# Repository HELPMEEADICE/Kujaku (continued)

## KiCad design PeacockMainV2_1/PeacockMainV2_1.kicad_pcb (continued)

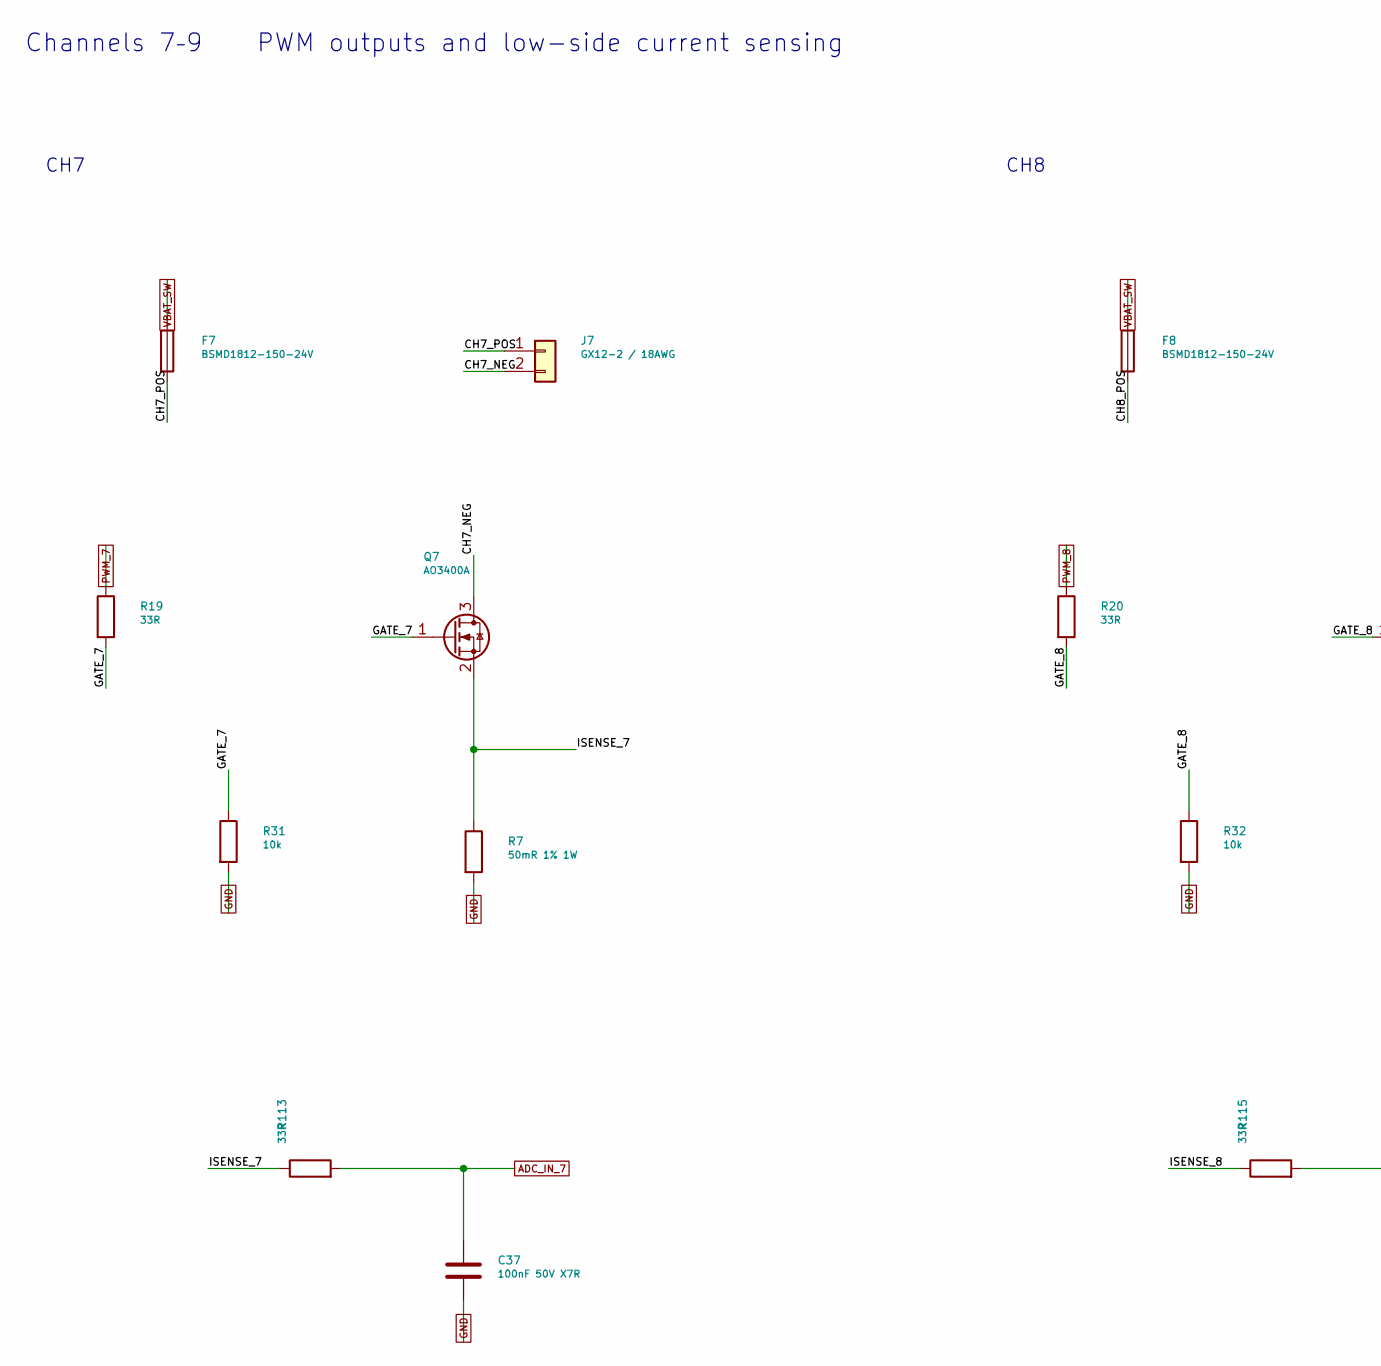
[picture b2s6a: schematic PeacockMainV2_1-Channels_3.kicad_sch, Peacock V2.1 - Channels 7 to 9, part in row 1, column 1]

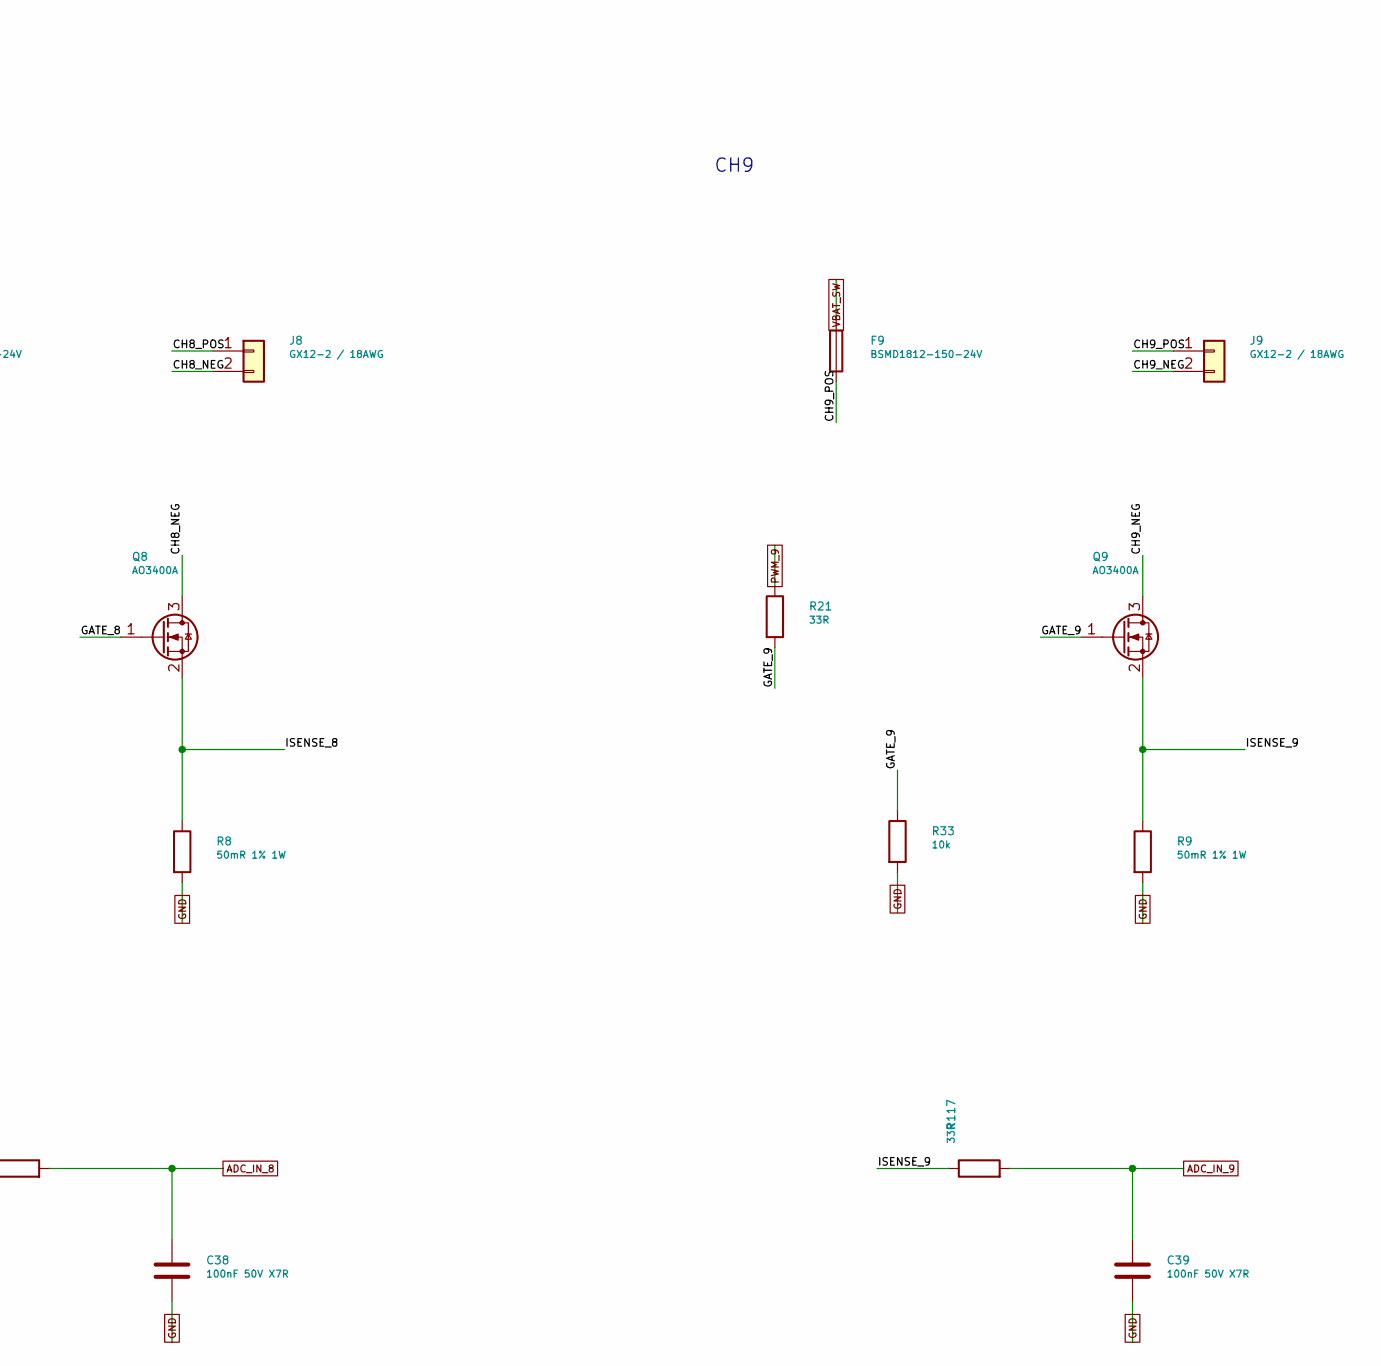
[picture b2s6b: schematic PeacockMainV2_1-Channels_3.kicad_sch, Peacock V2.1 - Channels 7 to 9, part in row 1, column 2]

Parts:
C37, C38, C39: 100nF 50V X7R; C_0603_1608Metric; MPN CC0603KRX7R9BB104; LCSC C14663
F7, F8, F9: BSMD1812-150-24V; R_1812_4532Metric; MPN BSMD1812-150-24V; LCSC C883153
J7, J8, J9: GX12-2 / 18AWG; GX12_Leadout_1x02_P5.00mm
Q7, Q8, Q9: AO3400A; SOT-23; MPN AO3400A; LCSC C20917
R7, R8, R9: 50mR 1% 1W; R_1206_3216Metric; MPN FRM121WFR050TM; LCSC C7467249
R19, R20, R21, R113, R115, R117: 33R; R_0603_1608Metric; MPN 0603WAF330JT5E; LCSC C23140
R31, R32, R33: 10k; R_0603_1608Metric; MPN 0603WAF1002T5E; LCSC C25804

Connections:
/Channels 3/CH7_NEG: J7.2, Q7.3 (D)
/Channels 3/CH7_POS: F7.2, J7.1
/Channels 3/CH8_NEG: J8.2, Q8.3 (D)
/Channels 3/CH8_POS: F8.2, J8.1
/Channels 3/CH9_NEG: J9.2, Q9.3 (D)
/Channels 3/CH9_POS: F9.2, J9.1
/Channels 3/GATE_7: Q7.1 (G), R19.2, R31.1
/Channels 3/GATE_8: Q8.1 (G), R20.2, R32.1
/Channels 3/GATE_9: Q9.1 (G), R21.2, R33.1
/Channels 3/ISENSE_7: Q7.2 (S), R7.1, R113.1
/Channels 3/ISENSE_8: Q8.2 (S), R8.1, R115.1
/Channels 3/ISENSE_9: Q9.2 (S), R9.1, R117.1
ADC_IN_7: C37.1, R113.2; also elsewhere on the board
ADC_IN_8: C38.1, R115.2; also elsewhere on the board
ADC_IN_9: C39.1, R117.2; also elsewhere on the board
GND: C37.2, C38.2, C39.2, R7.2, R8.2, R9.2, R31.2, R32.2, R33.2; also elsewhere on the board
PWM_7: R19.1; also elsewhere on the board
PWM_8: R20.1; also elsewhere on the board
PWM_9: R21.1; also elsewhere on the board
VBAT_SW: F7.1, F8.1, F9.1; also elsewhere on the board

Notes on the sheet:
Channels 7–9 PWM outputs and low-side current sensing
CH7
CH8
CH9

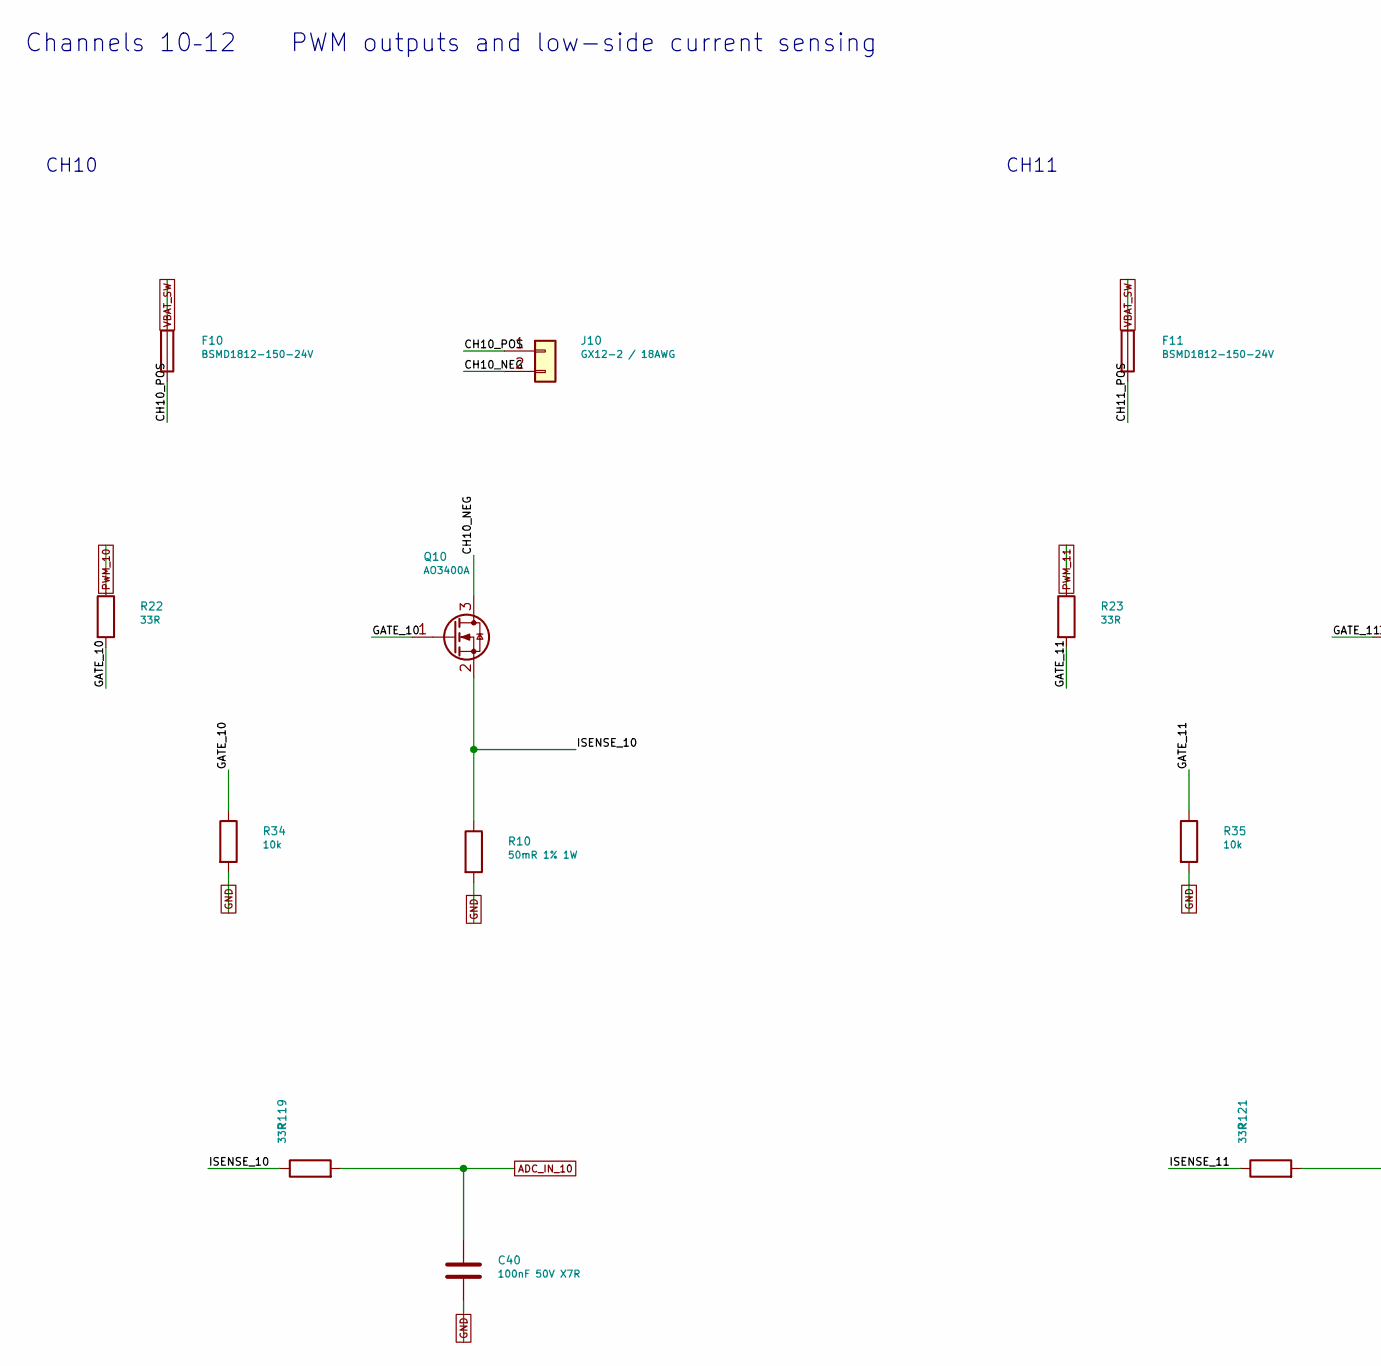
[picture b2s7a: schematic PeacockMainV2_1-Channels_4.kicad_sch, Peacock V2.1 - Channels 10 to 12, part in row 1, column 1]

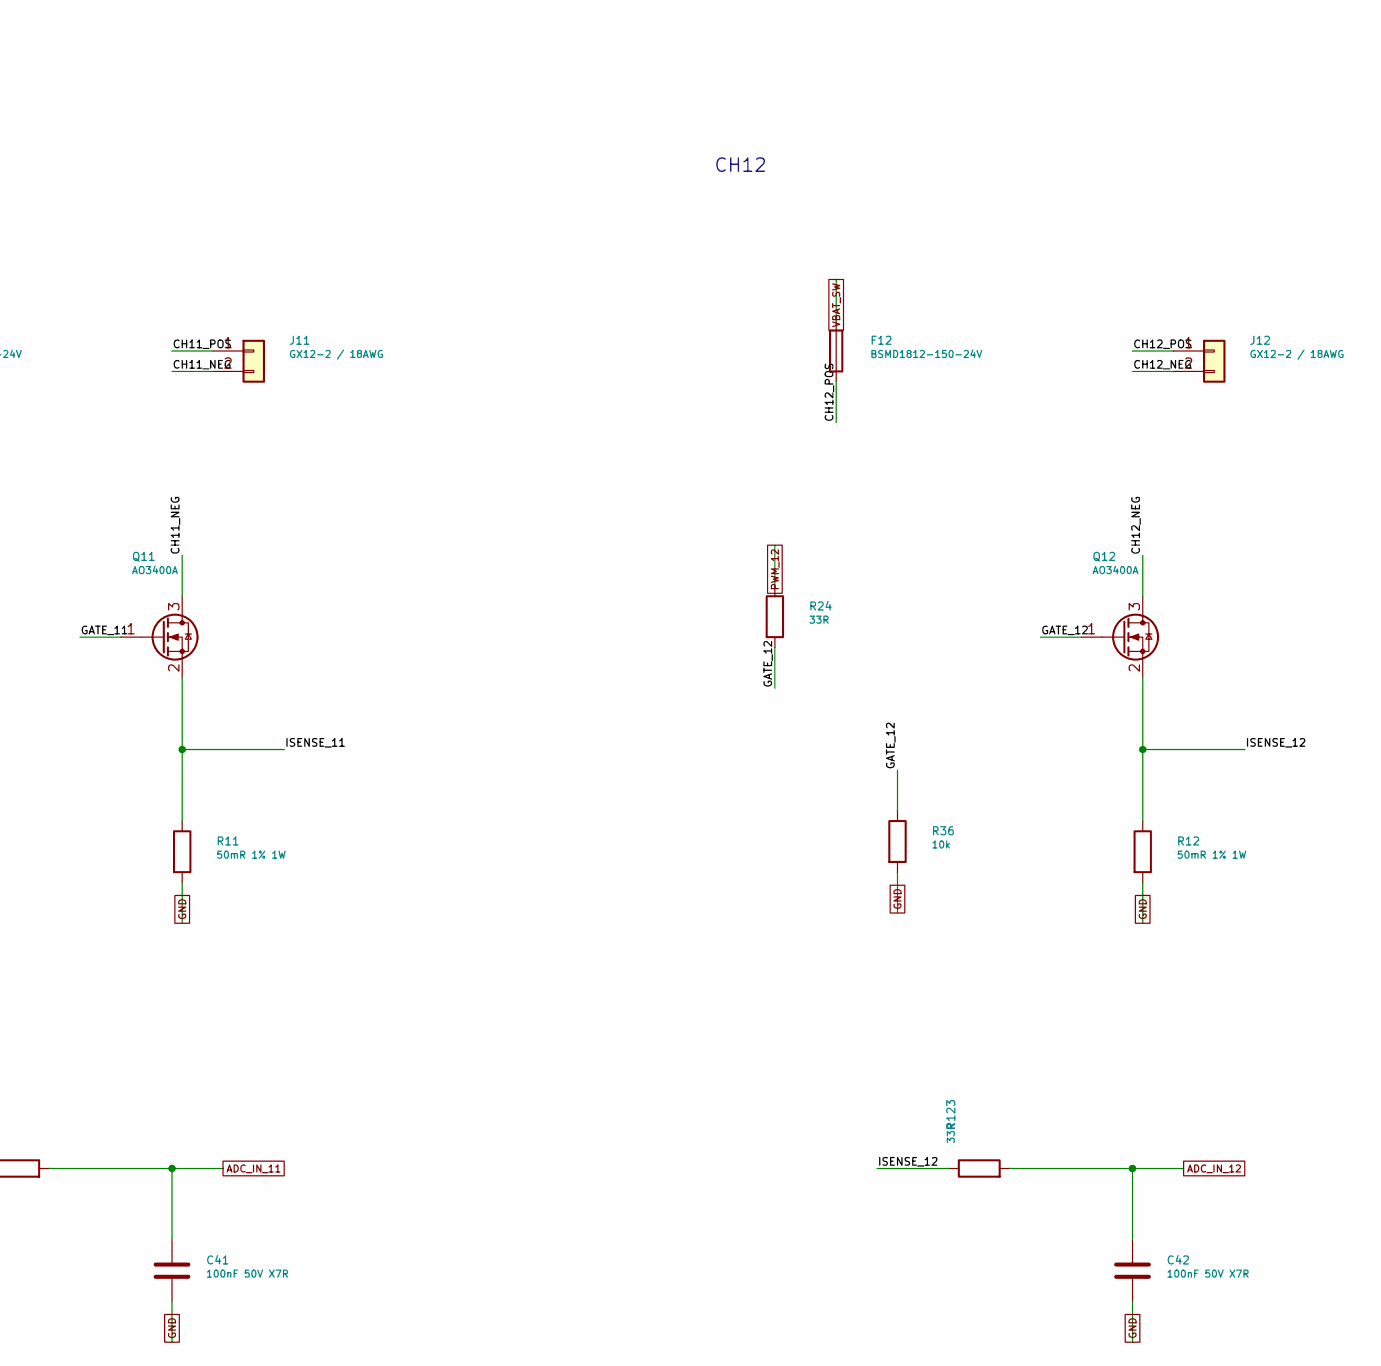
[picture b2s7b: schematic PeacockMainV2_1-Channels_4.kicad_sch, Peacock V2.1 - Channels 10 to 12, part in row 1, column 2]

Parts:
C40, C41, C42: 100nF 50V X7R; C_0603_1608Metric; MPN CC0603KRX7R9BB104; LCSC C14663
F10, F11, F12: BSMD1812-150-24V; R_1812_4532Metric; MPN BSMD1812-150-24V; LCSC C883153
J10, J11, J12: GX12-2 / 18AWG; GX12_Leadout_1x02_P5.00mm
Q10, Q11, Q12: AO3400A; SOT-23; MPN AO3400A; LCSC C20917
R10, R11, R12: 50mR 1% 1W; R_1206_3216Metric; MPN FRM121WFR050TM; LCSC C7467249
R22, R23, R24, R119, R121, R123: 33R; R_0603_1608Metric; MPN 0603WAF330JT5E; LCSC C23140
R34, R35, R36: 10k; R_0603_1608Metric; MPN 0603WAF1002T5E; LCSC C25804

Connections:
/Channels 4/CH10_NEG: J10.2, Q10.3 (D)
/Channels 4/CH10_POS: F10.2, J10.1
/Channels 4/CH11_NEG: J11.2, Q11.3 (D)
/Channels 4/CH11_POS: F11.2, J11.1
/Channels 4/CH12_NEG: J12.2, Q12.3 (D)
/Channels 4/CH12_POS: F12.2, J12.1
/Channels 4/GATE_10: Q10.1 (G), R22.2, R34.1
/Channels 4/GATE_11: Q11.1 (G), R23.2, R35.1
/Channels 4/GATE_12: Q12.1 (G), R24.2, R36.1
/Channels 4/ISENSE_10: Q10.2 (S), R10.1, R119.1
/Channels 4/ISENSE_11: Q11.2 (S), R11.1, R121.1
/Channels 4/ISENSE_12: Q12.2 (S), R12.1, R123.1
ADC_IN_10: C40.1, R119.2; also elsewhere on the board
ADC_IN_11: C41.1, R121.2; also elsewhere on the board
ADC_IN_12: C42.1, R123.2; also elsewhere on the board
GND: C40.2, C41.2, C42.2, R10.2, R11.2, R12.2, R34.2, R35.2, R36.2; also elsewhere on the board
PWM_10: R22.1; also elsewhere on the board
PWM_11: R23.1; also elsewhere on the board
PWM_12: R24.1; also elsewhere on the board
VBAT_SW: F10.1, F11.1, F12.1; also elsewhere on the board

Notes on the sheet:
Channels 10–12 PWM outputs and low-side current sensing
CH10
CH11
CH12

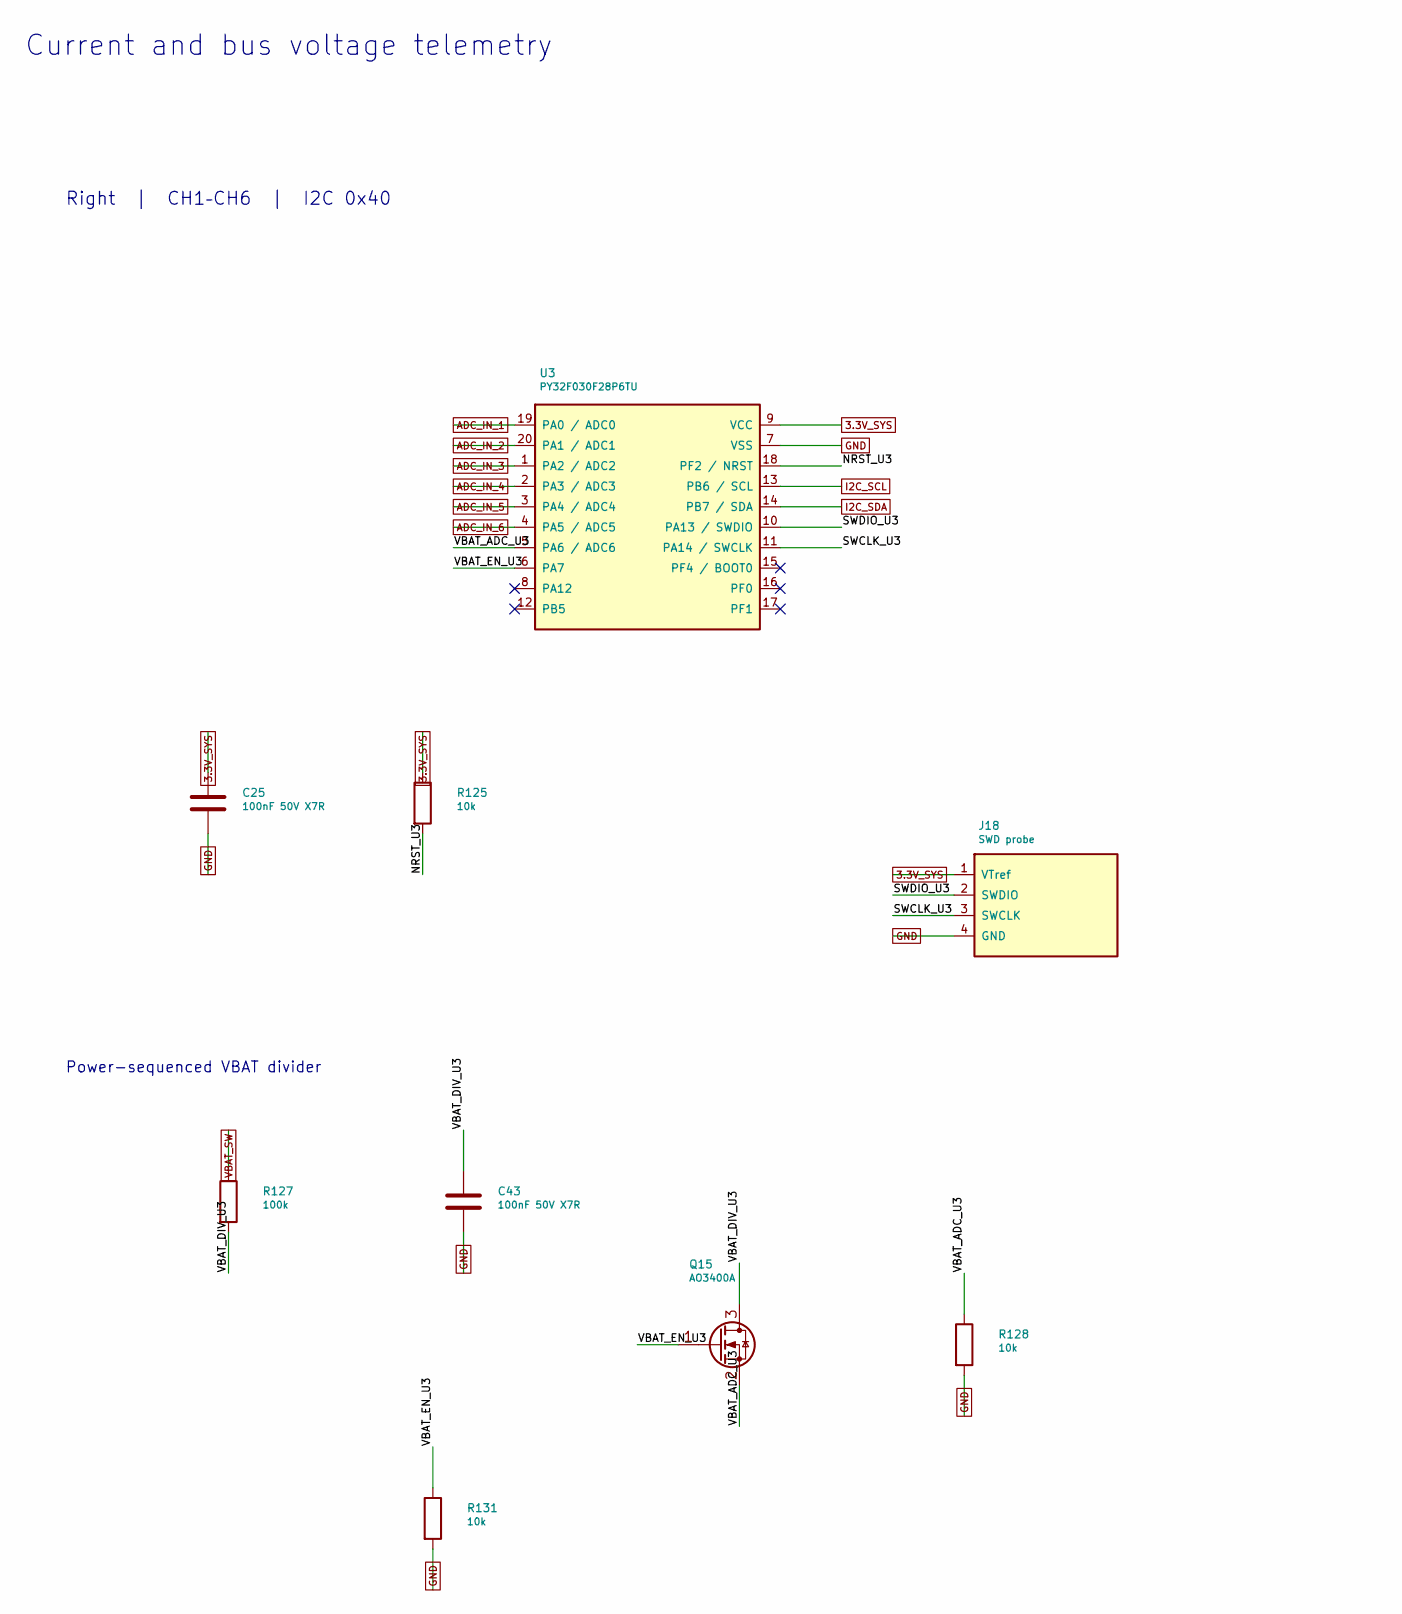
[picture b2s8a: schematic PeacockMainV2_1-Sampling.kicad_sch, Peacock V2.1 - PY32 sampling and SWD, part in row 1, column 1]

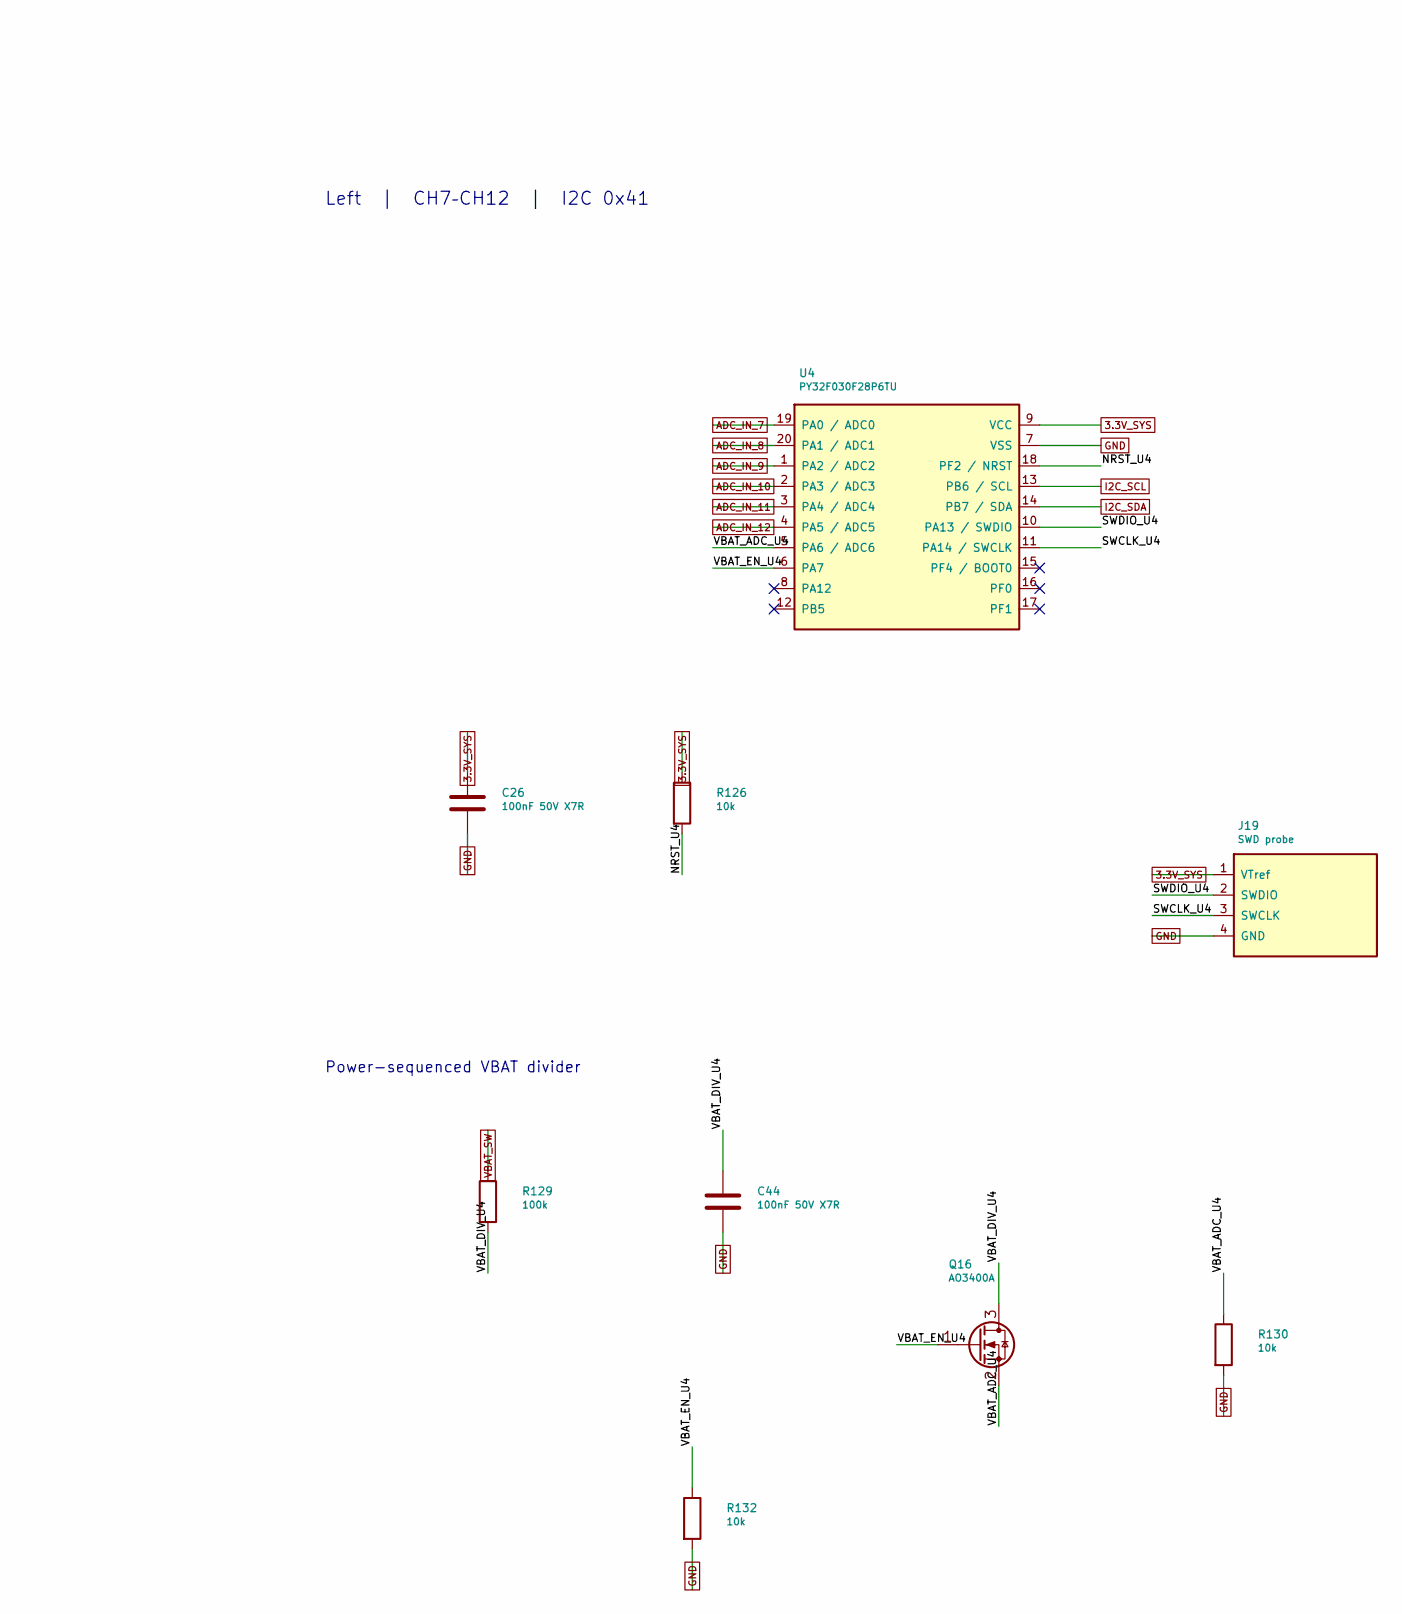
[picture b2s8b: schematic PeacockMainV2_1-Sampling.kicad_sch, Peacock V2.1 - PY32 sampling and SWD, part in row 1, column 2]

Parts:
C25, C26, C43, C44: 100nF 50V X7R; C_0603_1608Metric; MPN CC0603KRX7R9BB104; LCSC C14663
J18, J19: SWD probe; SWD_Probe_1x04_P1.27mm
Q15, Q16: AO3400A; SOT-23; MPN AO3400A; LCSC C20917
R125, R126, R128, R130, R131, R132: 10k; R_0603_1608Metric; MPN 0603WAF1002T5E; LCSC C25804
R127, R129: 100k; R_0603_1608Metric; MPN 0603WAF1003T5E; LCSC C25803
U3, U4: PY32F030F28P6TU; TSSOP-20_4.4x6.5mm_P0.65mm; MPN PY32F030F28P6TU; LCSC C3018716

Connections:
3.3V_SYS: C25.1, C26.1, J18.1 (VTref), J19.1 (VTref), R125.1, R126.1, U3.9 (VCC), U4.9 (VCC); also elsewhere on the board
/Sampling/NRST_U3: R125.2, U3.18 (PF2_/_NRST)
/Sampling/NRST_U4: R126.2, U4.18 (PF2_/_NRST)
/Sampling/SWCLK_U3: J18.3 (SWCLK), U3.11 (PA14_/_SWCLK)
/Sampling/SWCLK_U4: J19.3 (SWCLK), U4.11 (PA14_/_SWCLK)
/Sampling/SWDIO_U3: J18.2 (SWDIO), U3.10 (PA13_/_SWDIO)
/Sampling/SWDIO_U4: J19.2 (SWDIO), U4.10 (PA13_/_SWDIO)
/Sampling/VBAT_ADC_U3: Q15.2 (S), R128.1, U3.5 (PA6_/_ADC6)
/Sampling/VBAT_ADC_U4: Q16.2 (S), R130.1, U4.5 (PA6_/_ADC6)
/Sampling/VBAT_DIV_U3: C43.1, Q15.3 (D), R127.2
/Sampling/VBAT_DIV_U4: C44.1, Q16.3 (D), R129.2
/Sampling/VBAT_EN_U3: Q15.1 (G), R131.1, U3.6 (PA7)
/Sampling/VBAT_EN_U4: Q16.1 (G), R132.1, U4.6 (PA7)
ADC_IN_1: U3.19 (PA0_/_ADC0); also elsewhere on the board
ADC_IN_2: U3.20 (PA1_/_ADC1); also elsewhere on the board
ADC_IN_3: U3.1 (PA2_/_ADC2); also elsewhere on the board
ADC_IN_4: U3.2 (PA3_/_ADC3); also elsewhere on the board
ADC_IN_5: U3.3 (PA4_/_ADC4); also elsewhere on the board
ADC_IN_6: U3.4 (PA5_/_ADC5); also elsewhere on the board
ADC_IN_7: U4.19 (PA0_/_ADC0); also elsewhere on the board
ADC_IN_8: U4.20 (PA1_/_ADC1); also elsewhere on the board
ADC_IN_9: U4.1 (PA2_/_ADC2); also elsewhere on the board
ADC_IN_10: U4.2 (PA3_/_ADC3); also elsewhere on the board
ADC_IN_11: U4.3 (PA4_/_ADC4); also elsewhere on the board
ADC_IN_12: U4.4 (PA5_/_ADC5); also elsewhere on the board
GND: C25.2, C26.2, C43.2, C44.2, J18.4 (GND), J19.4 (GND), R128.2, R130.2, R131.2, R132.2, U3.7 (VSS), U4.7 (VSS); also elsewhere on the board
I2C_SCL: U3.13 (PB6_/_SCL), U4.13 (PB6_/_SCL); also elsewhere on the board
I2C_SDA: U3.14 (PB7_/_SDA), U4.14 (PB7_/_SDA); also elsewhere on the board
VBAT_SW: R127.1, R129.1; also elsewhere on the board

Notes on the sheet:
Current and bus voltage telemetry
Right | CH1–CH6 | I2C 0x40
Power-sequenced VBAT divider
Left | CH7–CH12 | I2C 0x41

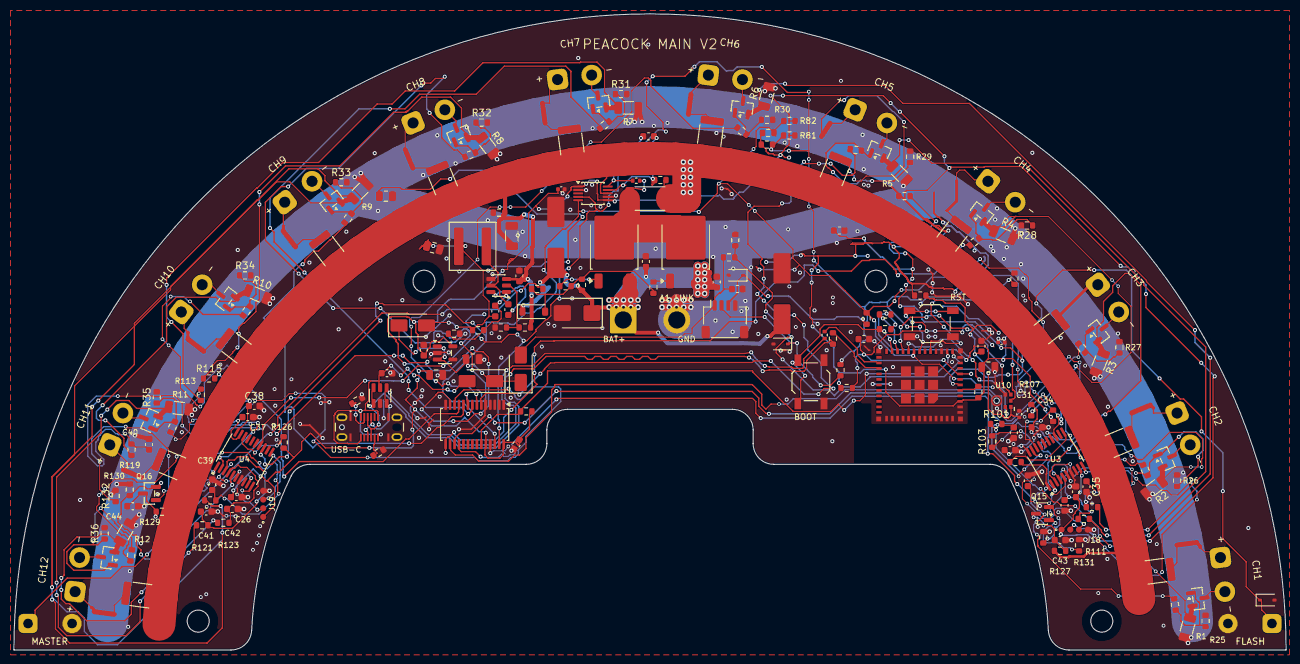
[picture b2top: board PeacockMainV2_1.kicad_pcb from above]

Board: 2 copper layers, 185.0 x 92.5 mm, 199 parts (0 on the bottom side), 124 nets.

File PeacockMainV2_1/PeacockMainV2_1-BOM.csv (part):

Reference,Qty,Value,Footprint,Manufacturer,MPN,LCSC,SMT_Populate,JLCPCB Library,Datasheet,Assembly Notes
"C1,C2",2,220uF 25V,PeacockMainV2_1:Cap_8x10p5,Panasonic,EEH-ZA1E221P,,No,N/A,https://na.industrial.panasonic.com/products/capacitors/alum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,Hand solder. Panasonic MPN. No LCSC number verified.
"C3,C4,C6,C7,C13,C14,C19,C20,C25,C26,C31,C32,C33,C34,C35,C36,C37,C38,C39,C40,C41,C42,C43,C44",24,100nF 50V X7R,Capacitor_SMD:C_0603_1608Metric,YAGEO,CC0603KRX7R9BB104,C14663,Yes,Basic,https://jlcpcb.com/api/file/downloadByFileSystemAccessId/866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,
C5,1,22uF 25V X5R,Capacitor_SMD:C_1206_3216Metric,Samsung Electro Mechanics,CL31A226KAHNNNE,C12891,Yes,Basic,https://jlcpcb.com/api/file/downloadByFileSystemAccessId/858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,
"C8,C9,C12",3,22uF 25V X5R,Capacitor_SMD:C_0805_2012Metric,Samsung Electro Mechanics,CL21A226MAQNNNE,C45783,Yes,Basic,https://jlcpcb.com/api/file/downloadByFileSystemAccessId/857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,
C10,1,100pF 50V C0G,Capacitor_SMD:C_0603_1608Metric,Samsung Electro Mechanics,CL10C101JB8NNNC,C14858,Yes,Basic,https://jlcpcb.com/api/file/downloadByFileSystemAccessId/857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,
"C11,C16",2,10uF 25V X5R,Capacitor_SMD:C_0805_2012Metric,Samsung Electro Mechanics,CL21A106KAYNNNE,C15850,Yes,Basic,https://jlcpcb.com/api/file/downloadByFileSystemAccessId/857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,
"C15,C17,C21",3,100nF 50V X7R,Capacitor_SMD:C_0402_1005Metric,Samsung Electro Mechanics,CL05B104KB54PNC,C307331,Yes,Basic,https://jlcpcb.com/api/file/downloadByFileSystemAccessId/855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,
"C18,C22,C23,C24",4,1uF 50V X5R,Capacitor_SMD:C_0603_1608Metric,Samsung Electro Mechanics,CL10A105KB8NNNC,C15849,Yes,Basic,https://jlcpcb.com/api/file/downloadByFileSystemAccessId/855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,
D1,1,SMBJ15A,Diode_SMD:D_SMB,hongjiacheng,SMBJ15A,C19077569,Yes,Preferred,https://jlcpcb.com/api/file/downloadByFileSystemAccessId/875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,
D2,1,BZT52C12,Diode_SMD:D_SOD-123,hongjiacheng,BZT52C12,C19077410,Yes,Preferred,https://jlcpcb.com/api/file/downloadByFileSystemAccessId/875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,
"D3,D4,D5",3,SS34,Diode_SMD:D_SMA,MDD Microdiode Semiconductor,SS34,C8678,Yes,Basic,https://jlcpcb.com/api/file/downloadByFileSystemAccessId/858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,
D6,1,USBLC6-2SC6-ES,Package_TO_SOT_SMD:SOT-23-6,ElecSuper,USBLC6-2SC6-ES,C5180249,Yes,Extended,https://atta.szlcsc.com/upload/public/pdf/source/20250407/0D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,
"D7,D8,D9",3,H3V3SD3B,Diode_SMD:D_SOD-323,R+O hongjiacheng,H3V3SD3B,C20615802,Yes,Preferred,https://item.szlcsc.com/21979977.html,Economic preferred extended per catalogue snapshot.
"F1,F2,F3,F4,F5,F6,F7,F8,F9,F10,F11,F12",12,BSMD1812-150-24V,Resistor_SMD:R_1812_4532Metric,BHFUSE,BSMD1812-150-24V,C883153,Yes,Extended,https://jlcpcb.com/api/file/downloadByFileSystemAccessId/858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,
"H1,H2,H3,H4",4,M3 / 3.2mm,MountingHole:MountingHole_3.2mm_M3,,,,No,N/A,,NPTH enclosure hardware.
"J1,J2,J3,J4,J5,J6,J7,J8,J9,J10,J11,J12",12,GX12-2 / 18AWG,PeacockMainV2_1:GX12_Leadout_1x02_P5.00mm,,,,No,N/A,,Hand solder wiring to bare PCB pads.
J13,1,BATTERY 16AWG,PeacockMainV2_1:Battery_16AWG,,,,No,N/A,,Hand solder wiring to bare PCB pads.
J14,1,MASTER,PeacockMainV2_1:Remote_Switch,,,,No,N/A,,Hand solder wiring to bare PCB pads.
J15,1,FLASH,PeacockMainV2_1:Remote_Switch,,,,No,N/A,,Hand solder wiring to bare PCB pads.
J16,1,USB4145-03-0170-C,PeacockMainV2_1:USB_C_Receptacle_GCT_USB4145-03-0170-C_Vertical,GCT,USB4145-03-0170-C,C5181332,No,Extended,https://xonstorage.z8.web.core.windows.net/pdf/gct_usb414503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,Hand solder. Vertical mating direction +Z. Four plated shell slots.
J17,1,A1002WR-S-4P,Connector_JST:JST_SH_SM04B-SRSS-TB_1x04-1MP_P1.00mm_Horizontal,CJT Changjiang Connectors,A1002WR-S-4P,C239522,Yes,Extended,https://pese.oss-cn-shenzhen.aliyuncs.com/pdfs/2010160407_CJ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,"CJT SH-compatible side-entry, 1.00 mm. Verify mating to the A2 harness on first article."
"J18,J19",2,SWD probe,PeacockMainV2_1:SWD_Probe_1x04_P1.27mm,,,,No,N/A,,Bare top-side SWD contacts. No component or stencil aperture. Pin 1 is VTref.
L1,1,10uH,Inductor_SMD:L_Coilcraft_XAL6060-XXX,YJYCOIN,YSPIT0660A-100M,C18199451,Yes,Extended,https://jlcpcb.com/api/file/downloadByFileSystemAccessId/860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,
"Q1,Q2,Q3,Q4,Q5,Q6,Q7,Q8,Q9,Q10,Q11,Q12,Q15,Q16",14,AO3400A,Package_TO_SOT_SMD:SOT-23,Alpha Omega Semicon,AO3400A,C20917,Yes,Basic,https://jlcpcb.com/api/file/downloadByFileSystemAccessId/855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,
"Q13,Q14",2,HY19P03D,Package_TO_SOT_SMD:TO-252-2,HUAYI,HY19P03D,C122492,Yes,Extended,https://jlcpcb.com/api/file/downloadByFileSystemAccessId/858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,
"R1,R2,R3,R4,R5,R6,R7,R8,R9,R10,R11,R12",12,50mR 1% 1W,Resistor_SMD:R_1206_3216Metric,FOJAN,FRM121WFR050TM,C7467249,Yes,Extended,https://jlcpcb.com/partdetail/FOJAN-FRM121WFR050TM/C7467249,
"R13,R14,R15,R16,R17,R18,R19,R20,R21,R22,R23,R24,R53,R54,R72,R75,R76,R101,R103,R105,R107,R109,R111,R113,R115,R117,R119,R121,R123",29,33R,Resistor_SMD:R_0603_1608Metric,UNI ROYAL Uniroyal Elec,0603WAF330JT5E,C23140,Yes,Basic,https://jlcpcb.com/api/file/downloadByFileSystemAccessId/857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,
"R25,R26,R27,R28,R29,R30,R31,R32,R33,R34,R35,R36,R61,R64,R65,R66,R67,R68,R69,R70,R125,R126,R128,R130,R131,R132",26,10k,Resistor_SMD:R_0603_1608Metric,UNI ROYAL Uniroyal Elec,0603WAF1002T5E,C25804,Yes,Basic,https://jlcpcb.com/api/file/downloadByFileSystemAccessId/857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,
R49,1,2mR 1% 3W,Resistor_SMD:R_2512_6332Metric,Milliohm,HoLLR2512-3W-2mR-1%,C2994640,Yes,Extended,https://jlcpcb.com/api/file/downloadByFileSystemAccessId/858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,
"R50,R52,R56,R77,R127,R129",6,100k,Resistor_SMD:R_0603_1608Metric,UNI ROYAL Uniroyal Elec,0603WAF1003T5E,C25803,Yes,Basic,https://jlcpcb.com/api/file/downloadByFileSystemAccessId/857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,
"R51,R62,R63,R81,R82",5,5.1k,Resistor_SMD:R_0603_1608Metric,UNI ROYAL Uniroyal Elec,0603WAF5101T5E,C23186,Yes,Basic,https://jlcpcb.com/api/file/downloadByFileSystemAccessId/857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,
R55,1,510k,Resistor_SMD:R_0603_1608Metric,UNI ROYAL Uniroyal Elec,0603WAF5103T5E,C23192,Yes,Basic,https://jlcpcb.com/api/file/downloadByFileSystemAccessId/857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,
R57,1,75k,Resistor_SMD:R_0603_1608Metric,UNI ROYAL Uniroyal Elec,0603WAF7502T5E,C23242,Yes,Basic,https://jlcpcb.com/api/file/downloadByFileSystemAccessId/857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,"Existing Basic 75 kOhm upper feedback resistor, 1%."
R58,1,14.3k 0.1%,Resistor_SMD:R_0603_1608Metric,YAGEO,RT0603BRE0714K3L,C705810,Yes,Extended,https://item.szlcsc.com/742330.html,"Precision 14.3 kOhm lower feedback resistor, 0.1%."
R59,1,10R 1%,Resistor_SMD:R_0402_1005Metric,UNI ROYAL Uniroyal Elec,0402WGF100JTCE,C25077,Yes,Basic,https://jlcpcb.com/api/file/downloadByFileSystemAccessId/857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,
"R60,R78",2,10R 1%,Resistor_SMD:R_0603_1608Metric,UNI ROYAL Uniroyal Elec,0603WAF100JT5E,C22859,Yes,Basic,https://jlcpcb.com/api/file/downloadByFileSystemAccessId/857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,
R71,1,33R,Resistor_SMD:R_0402_1005Metric,UNI ROYAL Uniroyal Elec,0402WGF330JTCE,C25105,Yes,Basic,https://jlcpcb.com/api/file/downloadByFileSystemAccessId/857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,
"R73,R74",2,5.1k 1%,Resistor_SMD:R_0603_1608Metric,UNI ROYAL Uniroyal Elec,0603WAF5101T5E,C23186,Yes,Basic,https://jlcpcb.com/api/file/downloadByFileSystemAccessId/857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,
SW1,1,SW_BOOT,Button_Switch_SMD:SW_SPST_TL3342,SHOU HAN,TS5216A 160gf,C2681484,Yes,Extended,https://jlcpcb.com/api/file/downloadByFileSystemAccessId/875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,
SW2,1,SW_RST,Button_Switch_SMD:SW_SPST_TL3342,SHOU HAN,TS5216A 160gf,C2681484,Yes,Extended,https://jlcpcb.com/api/file/downloadByFileSystemAccessId/875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,
U1,1,SCT2331TVBR,Package_TO_SOT_SMD:SOT-23-6,Silicon Content Technology,SCT2331TVBR,C509068,Yes,Extended,https://www.silicontent.com/uploads/20241212/058bf96053e3cb5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,"32 V, 3 A FPWM buck. Pinout and feedback network updated. Prototype load validation pending."
U2,1,ME6211C33M5G-N,Package_TO_SOT_SMD:SOT-23-5,MICRONE Nanjing Micro One Elec,ME6211C33M5G-N,C82942,Yes,Extended,https://jlcpcb.com/api/file/downloadByFileSystemAccessId/879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,
U3,1,PY32F030F28P6TU,Package_SO:TSSOP-20_4.4x6.5mm_P0.65mm,Puya Semiconductor,PY32F030F28P6TU,C3018716,Yes,Extended,https://www.puyasemi.com/gongye/2787.html,Program over SWD for 7-bit target address 0x40.
U4,1,PY32F030F28P6TU,Package_SO:TSSOP-20_4.4x6.5mm_P0.65mm,Puya Semiconductor,PY32F030F28P6TU,C3018716,Yes,Extended,https://www.puyasemi.com/gongye/2787.html,Program over SWD for 7-bit target address 0x41.
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
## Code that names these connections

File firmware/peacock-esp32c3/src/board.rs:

//! Main V2.1 control-sheet nets and A2 wiring.
use esp_hal::peripherals::{GPIO0, GPIO1, GPIO3, GPIO4, GPIO5, GPIO6, GPIO7, GPIO10};

pub type ChgDet = GPIO0<'static>;
pub type PwmOe = GPIO1<'static>;
pub type FlashButton = GPIO3<'static>;
pub type Sda = GPIO4<'static>;
pub type Scl = GPIO5<'static>;
pub type MicBclk = GPIO6<'static>;
pub type MicWs = GPIO7<'static>;
pub type MicData = GPIO10<'static>;

// Strap pull-ups, BOOT SW1, and native USB D-/D+. These are left to the chip.
pub const BOOT_STRAPS: [u8; 3] = [2, 8, 9];
pub const USB_SERIAL_JTAG: [u8; 2] = [18, 19];

pub const HUSB238: u8 = 0x08;
pub const TCA9534: u8 = 0x20;
pub const PY32_RIGHT: u8 = 0x40;
pub const PY32_LEFT: u8 = 0x41;
pub const TOTAL_MONITOR: u8 = 0x44;
pub const PCA9685: u8 = 0x60;
pub const BQ25798: u8 = 0x6b;
pub const PCA_ALL_CALL: u8 = 0x70;
pub const I2C_HZ: u32 = 250_000;

pub const CHANNEL_COUNT: usize = 12;
pub const PWM_MAX: u16 = 4095;
/// Logical CH1..CH12 -> physical LEDn, from the V2.1 netlist.
pub const PWM_CHANNELS: [usize; CHANNEL_COUNT] = [11, 10, 9, 8, 0, 1, 2, 3, 4, 5, 6, 7];

// Calibrated ADC at GPIO0, after the 1:2 divider.
pub const CHG_PRESENT_MV: u16 = 1_800;
pub const CHG_ABSENT_MV: u16 = 1_200;
// Effective pack availability and undervoltage hysteresis on VBAT_SW.
pub const BUS_ON_MV: u16 = 9_300;
pub const BUS_OFF_MV: u16 = 8_800;

pub const TOTAL_SOFT_MA: u32 = 18_000;
pub const TOTAL_SUSTAINED_MA: u32 = 15_000;
pub const TOTAL_CUTOFF_MA: u32 = 20_000;
pub const CHANNEL_SOFT_MA: u32 = 1_500;
pub const CHANNEL_CUTOFF_MA: u32 = 2_000;
pub const MAX_SIMULTANEOUS_CHANNELS: usize = (TOTAL_SOFT_MA / CHANNEL_CUTOFF_MA) as usize;
pub const CHARGE_DERATE_HALF_C: i16 = 130;
pub const CHARGE_RESUME_HALF_C: i16 = 120;
pub const SHOW_THERMAL_CUTOFF_HALF_C: i16 = 170;

pub fn i2c_name(address: u8) -> &'static str {
    match address {
        HUSB238 => "HUSB238",
        TCA9534 => "TCA9534",
        PY32_RIGHT => "PY32 right",
        PY32_LEFT => "PY32 left",
        TOTAL_MONITOR => "U7 total monitor",
        PCA9685 => "PCA9685",
        BQ25798 => "BQ25798",
        PCA_ALL_CALL => "PCA9685 All Call",
        _ => "other",
    }
}
